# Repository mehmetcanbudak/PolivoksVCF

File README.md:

PolivoksVCF

Adaptation of the adaptation (of the adaptation) of the Polivoks VCF.
This one is a 6HP SMD (0603) module based on stuff I found here: https://github.com/L71/PolivoksVCF

Status: never tested.

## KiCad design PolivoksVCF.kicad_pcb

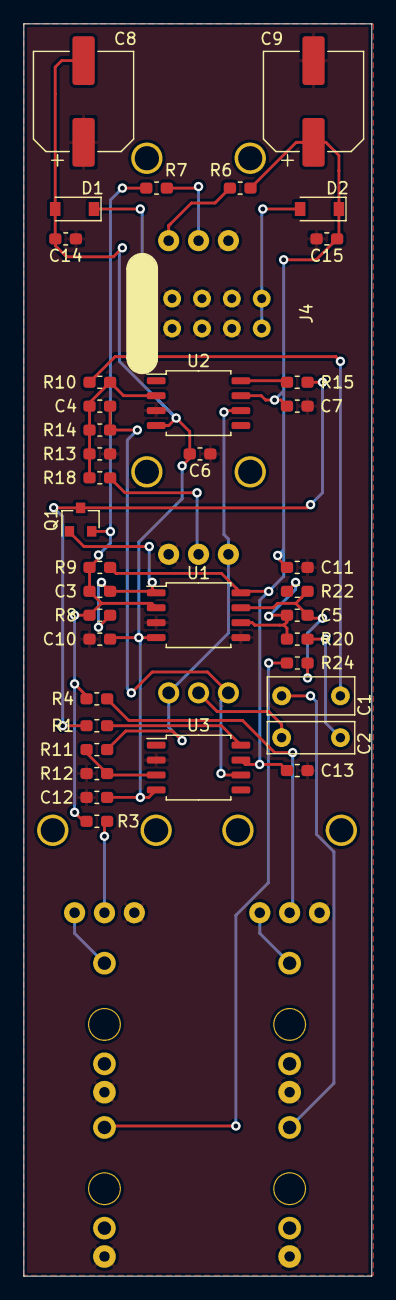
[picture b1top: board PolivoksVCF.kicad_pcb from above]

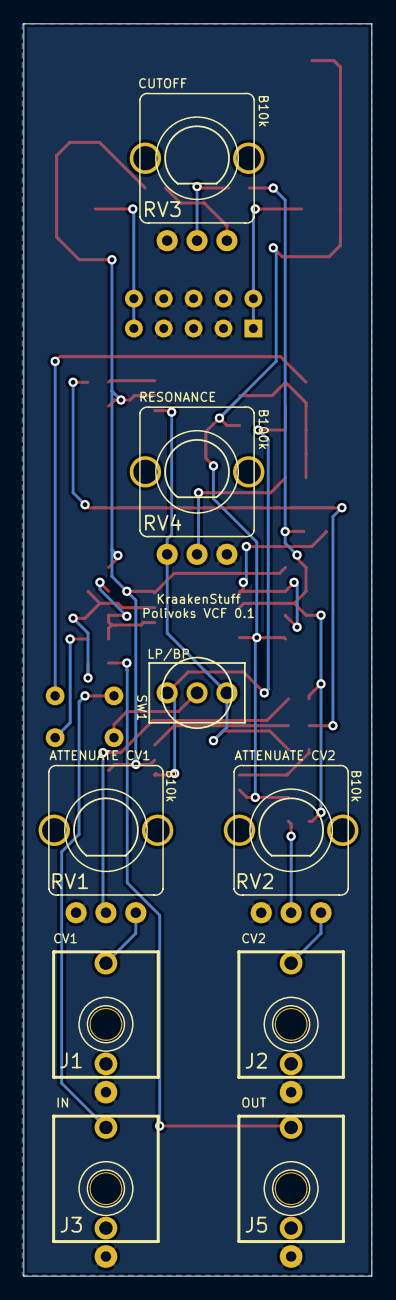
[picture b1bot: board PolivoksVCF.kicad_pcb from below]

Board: 2 copper layers, 29.6 x 106.5 mm, 48 parts (9 on the bottom side), 28 nets.

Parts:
C1: 220n; C_Rect_L7.2mm_W3.0mm_P5.00mm_FKS2_FKP2_MKS2_MKP2
C2: 100n; C_Rect_L7.2mm_W2.5mm_P5.00mm_FKS2_FKP2_MKS2_MKP2
C3, C4, C5: 100p; C_0603_1608Metric_Pad1.05x0.95mm_HandSolder
C6, C7, C10, C11, C12, C13, C14, C15: 100n; C_0603_1608Metric_Pad1.05x0.95mm_HandSolder
C8, C9: 10u; CP_Elec_8x6.9
D1, D2: 1N5819; D_SOD-123
J1: CV1; PJ301M-12
J2: CV2; PJ301M-12
J3: IN; PJ301M-12
J4: EuroPower; EuroHeader10
J5: OUT; PJ301M-12
Q1: 2N3904; SOT-23
R1, R15: 1M; R_0603_1608Metric_Pad1.05x0.95mm_HandSolder
R3, R4, R7, R9, R20, R22: 100k; R_0603_1608Metric_Pad1.05x0.95mm_HandSolder
R6: 10k; R_0603_1608Metric_Pad1.05x0.95mm_HandSolder
R8: 3.3k; R_0603_1608Metric_Pad1.05x0.95mm_HandSolder
R10, R11, R14: 47k; R_0603_1608Metric_Pad1.05x0.95mm_HandSolder
R12, R13, R24: 1k; R_0603_1608Metric_Pad1.05x0.95mm_HandSolder
R18: 33k; R_0603_1608Metric_Pad1.05x0.95mm_HandSolder
RV1, RV2, RV3: B10k; POT-9MM-ALPHA
RV4: B100k; POT-9MM-ALPHA
SW1: SW_SPDT; SubSwitch_SPDT
U1: TL072; SOIC-8_5.275x5.275mm_P1.27mm
U2, U3: LM4250; SOIC-8_5.275x5.275mm_P1.27mm

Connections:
+12V: C7.1, C9.1, C11.1, C13.1, C15.1, D2.1, R6.2, R9.2, U1.8, U2.7, U3.7
-12V: C6.2, C8.2, C10.2, C12.2, C14.2, D1.2, U1.4, U2.4, U3.4
GND: C6.1, C7.2, C8.1, C9.2, C10.1, C11.2, C12.1, C13.2, C14.1, C15.2, J1.S, J2.S, J3.S, J4.3, J4.4, J4.5, J4.6, J4.7, J4.8, J5.S, R12.1, R13.1, RV1.1, RV2.1, RV3.1, RV4.3, U1.3, U1.5, U2.3, U3.2
unnamed: C1.1, R10.2
unnamed: C1.2, J3.T
unnamed: C2.1, R20.1
unnamed: C2.2, SW1.2
unnamed: C3.1, Q1.1, R8.1, U1.1
unnamed: C3.2, Q1.2, R3.1, R4.1, R7.1, R8.2, R9.1, U1.2
unnamed: C4.1, R10.1, R13.2, R14.1, R18.2, U2.2
unnamed: C4.2, R14.2, SW1.1, U3.6
unnamed: C5.1, R22.2, R24.1, U1.7
unnamed: C5.2, R20.2, R22.1, U1.6
unnamed: D1.1, J4.1, J4.2
unnamed: D2.2, J4.9, J4.10
unnamed: J1.T, RV1.3
unnamed: J2.T, RV2.3
unnamed: J5.T, R24.2
unnamed: Q1.3, R1.2, R15.2
unnamed: R1.1, U3.8
unnamed: R3.2, RV2.2
unnamed: R4.2, RV1.2
unnamed: R6.1, RV3.3
unnamed: R7.2, RV3.2
unnamed: R11.1, RV4.1, SW1.3, U2.6
unnamed: R11.2, R12.2, U3.3
unnamed: R15.1, U2.8
unnamed: R18.1, RV4.2

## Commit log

2019-09-21 Added project files
2019-09-21 Added gerbers
2019-09-21 Added panel
2020-05-03 Small fix around power connector
2021-02-28 [ImgBot] Optimize images
    *Total -- 1,675.53kb -> 781.02kb (53.39%)
    /Art/Low pass1.png -- 43.07kb -> 17.47kb (59.45%)
    /Art/Band pass1.png -- 59.65kb -> 25.25kb (57.66%)
    /Art/Resonance.png -- 331.56kb -> 144.58kb (56.39%)
    /Art/Cutoff.png -- 478.60kb -> 211.30kb (55.85%)
    /Art/Polivoks.png -- 127.68kb -> 62.67kb (50.92%)
